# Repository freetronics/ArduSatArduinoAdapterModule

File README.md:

Freetronics ArduSat Arduino Adapter Module
==========================================
Copyright 2012 Freetronics Pty Ltd  
Freetronics site:  www.freetronics.com  
Freetronics email: info@freetronics.com  

CubeSat-compatible module that allows an Arduino or compatible board
to be plugged in upside down. All Arduino headers and CubeSat bus
headers are broken out to allow you to quickly hook any Arduino
model with Uno-compatible headers into a satellite stack.

Includes prototyping area to add your own parts.

Features:

 * CubeSat bus fully broken out, with CubeSat 5V and 3.3V duplicated.
 * Jumpers to allow easy linkage of Arduino and CubeSat power rails.
 * 5V and 3.3V "power on" LEDs.
 * Reset button connected to Arduino reset pin.
 * Parts overlay on both the top and the bottom so you can see what you
   are connecting without having to keep turning the board over.
 * Prototyping area.
 * Gold-plated PCB surface.

More information is available at:

  http://www.freetronics.com/asaam

INSTALLATION
------------
The design is saved as an EAGLE project. EAGLE PCB design software is
available from www.cadsoftusa.com free for non-commercial use. To use
this project download it and place the directory containing these files
into the "eagle" directory on your computer. Then open EAGLE and
navigate to Projects -> eagle -> ArduSatArduinoAdapterModule.

DISTRIBUTION
------------
The specific terms of distribution of this project are governed by the
license referenced below.

LICENSE
-------
Licensed under the TAPR Open Hardware License (www.tapr.org/OHL).
The "license" folder within this repository also contains a copy of
this license in plain text format.

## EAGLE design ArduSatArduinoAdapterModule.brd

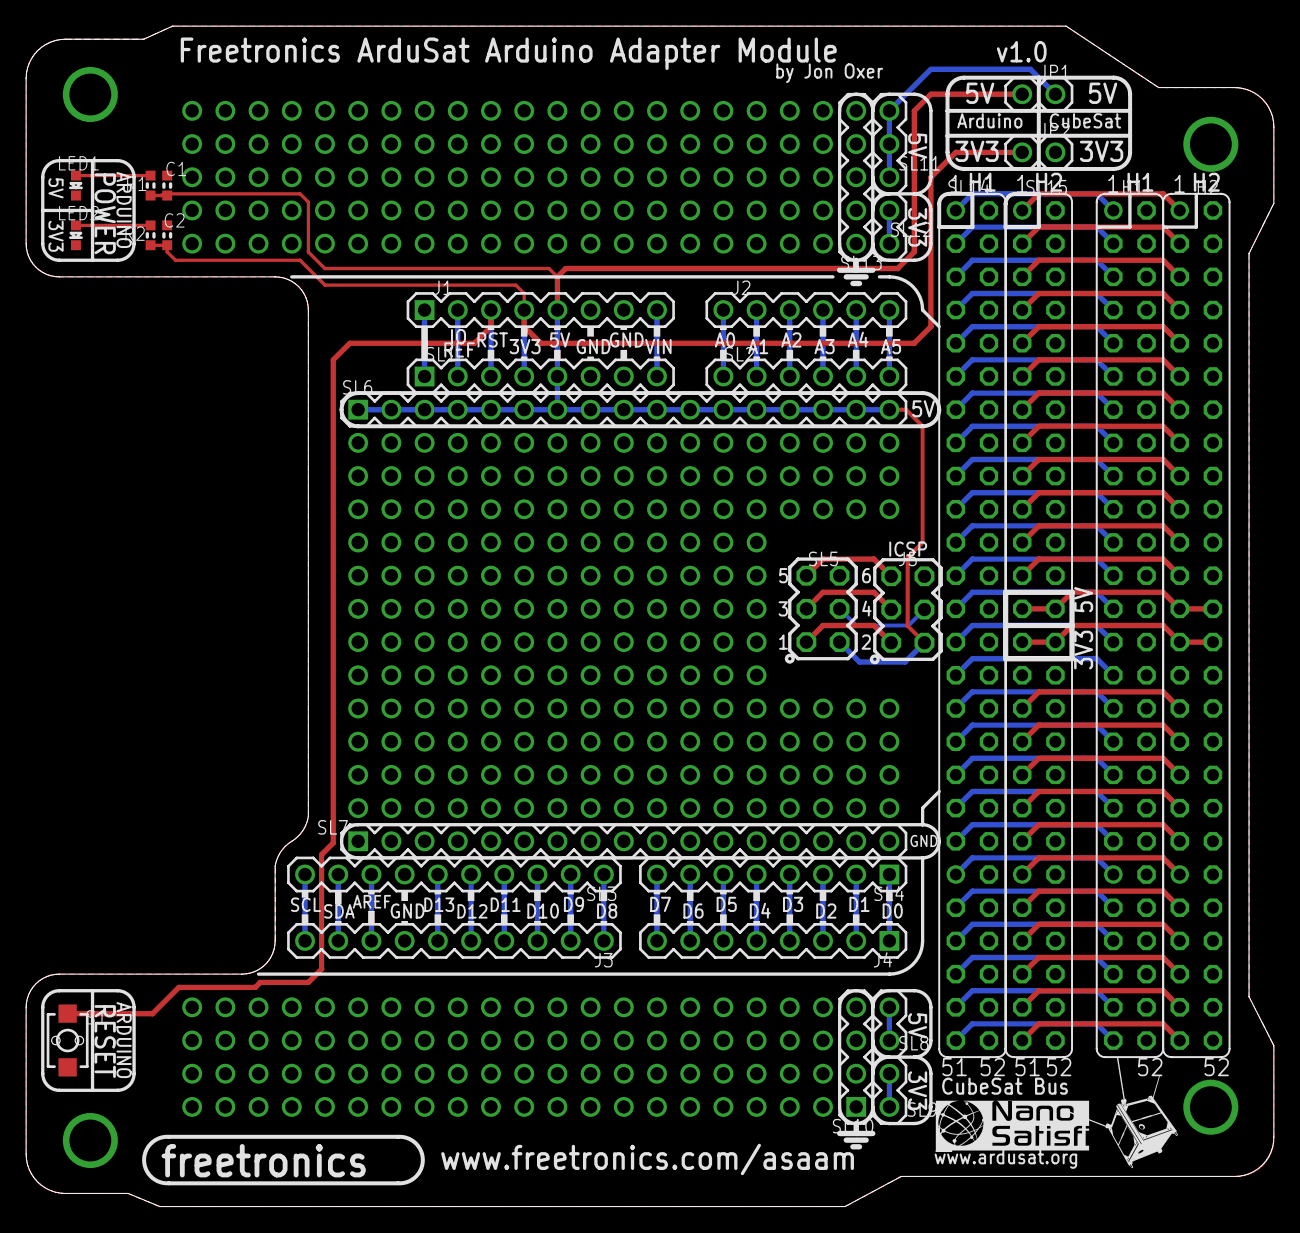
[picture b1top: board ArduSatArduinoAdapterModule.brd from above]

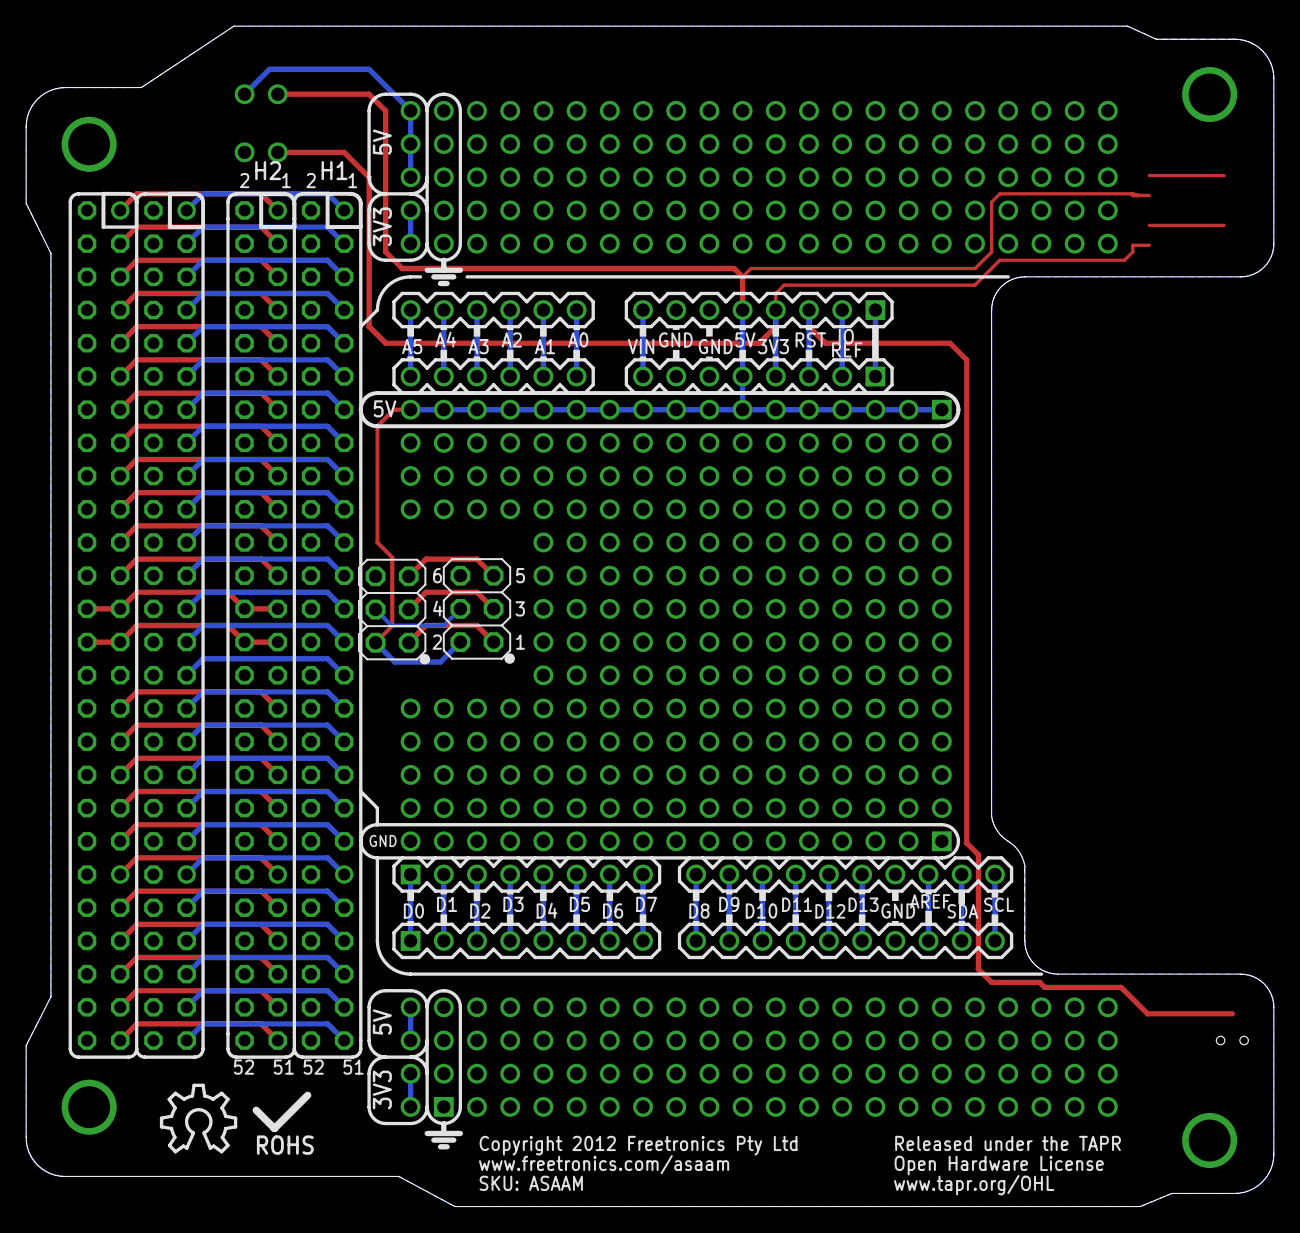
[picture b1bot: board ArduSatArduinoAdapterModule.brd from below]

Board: 4 copper layers, 95.5 x 90.3 mm, 36 parts (3 on the bottom side), 135 nets.

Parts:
C1, C2: 100nF 0603; 0603
H1, H2: CUBESATBUSH; CUBESATBUS
J1: Power; 1X08
J2: Analog; 1X06
J3: D8_13; 1X10
J4: D0_7; 1X08
J5: ICSP; 2X03PTH
JP1: 5V-LINK; 1X02
JP2: 3V3-LINK; 1X02
LED1: BLUE 0603; LED-0603
LED2: JADEGREEN 0603; LED-0603
MNT1, MNT2, MNT3, MNT4: HOLE3.2MM; HOLE32
R1: 2K2 0603; 0603
R2: 1K 0603; 0603
S1: RESET; TACTILE_SWITCH_SMD_2PIN_TINY
SL1: Power; 1X08
SL2: Analog; 1X06
SL3: D8_13; 1X10
SL4: D0_7; 1X08
SL5: ICSP-Breakout; 2X03PTH
SL6, SL7: M17; 1X17
SL8: +5V_SYS; 1X02
SL9, SL12: VCC_SYS; 1X02
SL10: GND; 1X04
SL11: +5V_SYS; 1X03
SL13: GND; 1X05
SL14: H1BREAKOUT; CUBESATBUS
SL15: H2BREAKOUT; CUBESATBUS
U$5: OSHW_10X200_NOTEXT

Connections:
3V3: C2.1, J1.4, JP2.2, R2.1, SL1.4
5V: C1.1, J1.5, J5.2, JP1.2, R1.1, SL1.5, SL5.2, SL6.1, SL6.2, SL6.3, SL6.4, SL6.5, SL6.6, SL6.7, SL6.8, SL6.9, SL6.10, SL6.11, SL6.12, SL6.13, SL6.14, SL6.15, SL6.16, SL6.17
+5V_SYS: H2.25, H2.26, JP1.1, SL8.1, SL8.2, SL11.1, SL11.2, SL11.3, SL15.25, SL15.26
A0: J2.1, SL2.1
A1: J2.2, SL2.2
A2: J2.3, SL2.3
A3: J2.4, SL2.4
A4: J2.5, SL2.5
A5: J2.6, SL2.6
AGND: H2.31, SL15.31
AREF: J3.8, SL3.8
D0_RX: J4.1, SL4.1
D1_TX: J4.2, SL4.2
D2: J4.3, SL4.3
D3: J4.4, SL4.4
D4: J4.5, SL4.5
D5: J4.6, SL4.6
D6: J4.7, SL4.7
D7: J4.8, SL4.8
D8: J3.1, SL3.1
D9: J3.2, SL3.2
D10: J3.3, SL3.3
D11_MOSI: J3.4, SL3.4
D12_MISO: J3.5, SL3.5
D13_SCK: J3.6, SL3.6
GND: C1.2, C2.2, H2.29, H2.30, H2.32, J1.6, J1.7, J3.7, J5.6, LED1.C, LED2.C, MNT1.P$1, MNT2.P$1, MNT3.P$1, MNT4.P$1, S1.1, SL1.6, SL1.7, SL3.7, SL5.6, SL7.1, SL7.2, SL7.3, SL7.4, SL7.5, SL7.6, SL7.7, SL7.8, SL7.9, SL7.10, SL7.11, SL7.12, SL7.13, SL7.14, SL7.15, SL7.16, SL7.17, SL10.1, SL10.2, SL10.3, SL10.4, SL13.1, SL13.2, SL13.3, SL13.4, SL13.5, SL15.29, SL15.30, SL15.32
H1L1: H1.1, SL14.1
H1L3: H1.3, SL14.3
H1L5: H1.5, SL14.5
H1L7: H1.7, SL14.7
H1L9: H1.9, SL14.9
H1L11: H1.11, SL14.11
H1L13: H1.13, SL14.13
H1L15: H1.15, SL14.15
H1L17: H1.17, SL14.17
H1L19: H1.19, SL14.19
H1L21: H1.21, SL14.21
H1L23: H1.23, SL14.23
H1L25: H1.25, SL14.25
H1L27: H1.27, SL14.27
H1L29: H1.29, SL14.29
H1L31: H1.31, SL14.31
H1L33: H1.33, SL14.33
H1L35: H1.35, SL14.35
H1L37: H1.37, SL14.37
H1L39: H1.39, SL14.39
H1L45: H1.45, SL14.45
H1L47: H1.47, SL14.47
H1L49: H1.49, SL14.49
H1L51: H1.51, SL14.51
H1R2: H1.2, SL14.2
H1R4: H1.4, SL14.4
H1R6: H1.6, SL14.6
H1R8: H1.8, SL14.8
H1R10: H1.10, SL14.10
H1R12: H1.12, SL14.12
H1R14: H1.14, SL14.14
H1R16: H1.16, SL14.16
H1R18: H1.18, SL14.18
H1R20: H1.20, SL14.20
H1R22: H1.22, SL14.22
H1R24: H1.24, SL14.24
H1R26: H1.26, SL14.26
H1R28: H1.28, SL14.28
H1R30: H1.30, SL14.30
H1R32: H1.32, SL14.32
H1R34: H1.34, SL14.34
H1R36: H1.36, SL14.36
H1R38: H1.38, SL14.38
H1R40: H1.40, SL14.40
H1R42: H1.42, SL14.42
H1R44: H1.44, SL14.44
H1R46: H1.46, SL14.46
H1R48: H1.48, SL14.48
H1R50: H1.50, SL14.50
H1R52: H1.52, SL14.52
H2L1: H2.1, SL15.1
H2L3: H2.3, SL15.3
H2L5: H2.5, SL15.5
H2L7: H2.7, SL15.7
H2L9: H2.9, SL15.9
H2L11: H2.11, SL15.11
H2L13: H2.13, SL15.13
H2L15: H2.15, SL15.15
H2L17: H2.17, SL15.17
H2L19: H2.19, SL15.19
H2L21: H2.21, SL15.21
H2L23: H2.23, SL15.23
H2L33: H2.33, SL15.33
H2L35: H2.35, SL15.35
H2L37: H2.37, SL15.37
H2L39: H2.39, SL15.39
H2L41: H2.41, SL15.41
H2L43: H2.43, SL15.43
H2L47: H2.47, SL15.47
H2R2: H2.2, SL15.2
H2R4: H2.4, SL15.4
H2R6: H2.6, SL15.6
H2R8: H2.8, SL15.8
H2R10: H2.10, SL15.10
H2R12: H2.12, SL15.12
H2R14: H2.14, SL15.14
H2R16: H2.16, SL15.16
H2R18: H2.18, SL15.18
H2R20: H2.20, SL15.20
H2R22: H2.22, SL15.22
H2R24: H2.24, SL15.24
H2R34: H2.34, SL15.34
H2R36: H2.36, SL15.36
H2R38: H2.38, SL15.38
H2R40: H2.40, SL15.40
H2R42: H2.42, SL15.42
H2R44: H2.44, SL15.44
H2R48: H2.48, SL15.48
H2R50: H2.50, SL15.50
H2R52: H2.52, SL15.52
IOREF: J1.2, SL1.2
unnamed: LED2.A, R2.2
unnamed: LED1.A, R1.2
unnamed: J5.4, SL5.4
unnamed: J5.1, SL5.1
unnamed: J5.3, SL5.3
unnamed: J5.5, SL5.5
RESET: J1.3, S1.2, SL1.3
RESVD: J1.1, SL1.1
SCL: J3.10, SL3.10
SCL2: H2.51, SL15.51
SCL_SYS: H1.43, SL14.43
SDA: J3.9, SL3.9
SDA2: H2.49, SL15.49
SDA_SYS: H1.41, SL14.41
VBATT45: H2.45, SL15.45
VBATT46: H2.46, SL15.46
VCC_SYS: H2.27, H2.28, JP2.1, SL9.1, SL9.2, SL12.1, SL12.2, SL15.27, SL15.28
VIN: J1.8, SL1.8

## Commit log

2012-12-11 Initial project import
2012-12-19 Switched to 4 layer PCB; completed all routing
2012-12-28 Added grounded corner mount holes and relocated some traces to inner layers to minimise risk of shorts to mounting sleeves
2018-03-22 Improved part label positions
2018-03-22 Fixed URL

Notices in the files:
parts and their libraries:
freetronics-original: Licensing: CC v3.0 Share-Alike You are welcome to use this library for commercial purposes.
